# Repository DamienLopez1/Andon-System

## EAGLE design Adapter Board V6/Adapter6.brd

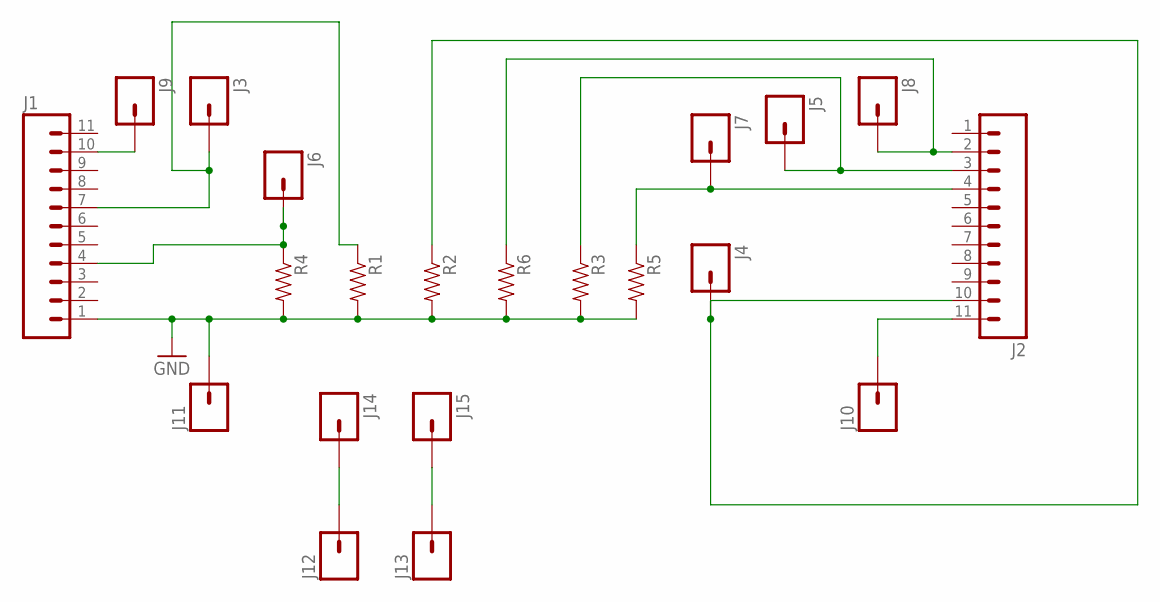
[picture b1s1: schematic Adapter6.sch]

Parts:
J1, J2: M11PTH; 1X11
J3, J4, J5, J6, J7, J8, J9, J12, J13: M01PTH_2MM; 1X01_2MM
J10, J11, J14, J15: M01PTH_NO_SILK_YES_STOP; 1X01_NO_SILK
R1, R2, R3, R4, R5, R6: RESISTOR1206; 1206

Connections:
GND: J1.1, J11.1, R1.2, R2.2, R3.2, R4.2, R5.2, R6.2
unnamed: J2.10, J4.1, R2.1
unnamed: J1.4, J6.1, R4.1
unnamed: J2.11, J10.1
unnamed: J2.4, J7.1, R5.1
unnamed: J2.3, J5.1, R3.1
unnamed: J2.2, J8.1, R6.1
unnamed: J1.10, J9.1
unnamed: J1.7, J3.1, R1.1
unnamed: J12.1, J14.1
unnamed: J13.1, J15.1

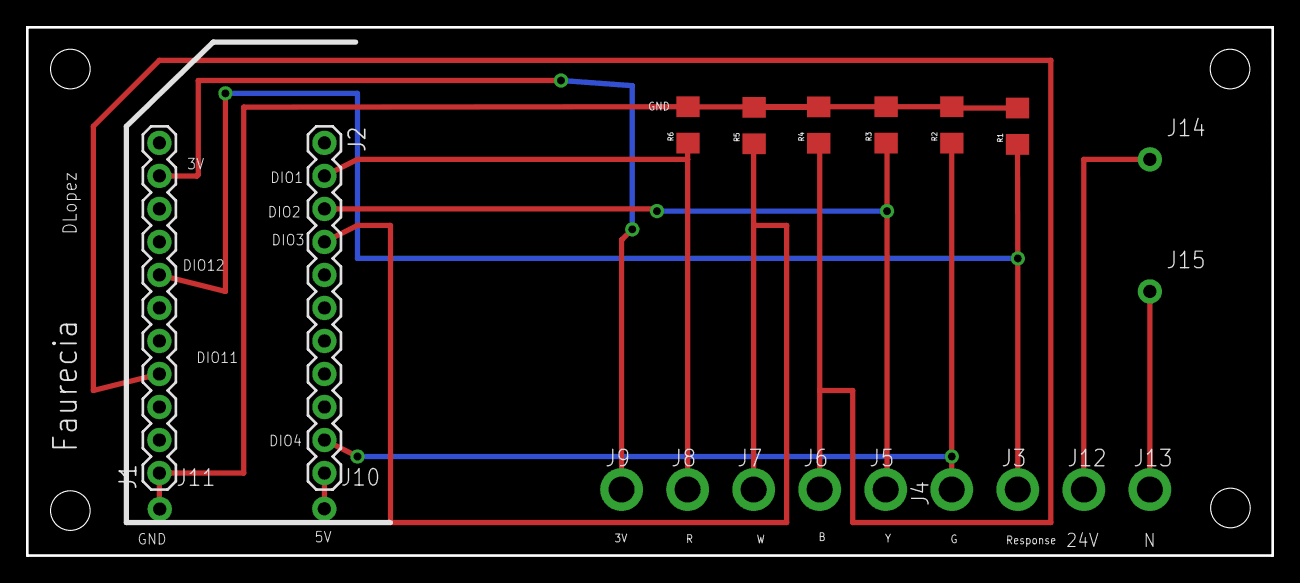
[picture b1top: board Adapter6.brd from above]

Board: 2 copper layers, 95.8 x 40.6 mm, 25 parts (0 on the bottom side), 11 nets.

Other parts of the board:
U$1, U$2, U$3, U$4: STAND-OFF-TIGHT

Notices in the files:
parts and their libraries:
SparkFun-Connectors: Licensing: Creative Commons ShareAlike 4.0 International - https://creativecommons.org/licenses/by-sa/4.0
